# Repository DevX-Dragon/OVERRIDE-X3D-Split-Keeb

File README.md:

# OVERRIDE-X3D Split Keeb
A split keyboard from-scratch, high-performance wireless split keyboard designed for ergonomic uses.

## Layout

## Renders
#### Assembled Render

#### PCB Render

## Firmware
This keyboard runs on **CircuitPython** using the **Adafruit HID library**. Unlike compiled firmware, you can edit your keymap by simply modifying the **code.py** file directly on the keyboard's internal storage.

#### Libraries
To run this firmware, you need the following libraries in your /lib folder:

**adafruit_hid** (For Keyboard and Consumer Control support)

**adafruit_ble** (For wireless Bluetooth connectivity)

## BOM
(note that this is where I purchased from, and some are bought in higher quanities then needed for cheaper prices and some websites are local-only)
| Product Name | Quantity | Source Link | Price |
| :--- | :--- | :--- | :--- |
| 1N4148 | 42 | [Link](https://www.duino.lk/product/x-1n4148-diode-in4148-4148-switching-diode/) | $0.60 |
| SK6812 MINI-E | 8 | [Link](http://www.aliexpress.com/item/1005008308801366.html) | $1.56 |
| 820K Ohms THT Resistor | 2 | [Link](https://www.duino.lk/product/820k-ohm-1-4w-820k-5-carbon-film-resistor/) | $0.30 |
| 1M Ohms THT Ressitor | 4 | [Link](https://www.duino.lk/product/1m-ohm-1-4w-1m-5-carbon-film-resistor/) | $0.30 |
| OUTEMU Red Switches | 42 | [Link](https://share.temu.com/CwgZ9XWDBxB) | $13.74 |
| Milk Theme XDA Key Caps | 42 | [Link](https://www.aliexpress.com/item/1005009136116760.html) | $10.83 |
| 800mAh 3.7V 501845P Battery | 2 | [Link](https://www.duino.lk/product/800mah-3-7v-501845p-lipo-battery/) | $3.00 |
| Seed Studio Seeed XIAO-nRF52840-Sense | 2 | [Link](https://www.aliexpress.com/item/1005007426899386.html) | $43.12 |
| **Total** | | | **$73.45** |

> The reason for using the Seed Studio Seeed XIAO-nRF52840-Sense is becuase thats the only compact MCU which has enough pins for this. The esp32-s3 is another alternative but doesnt have pins to control the LEDs. So I had to go with this. There are no other MCU thats fits in the same size and have the same amount of pins.

## Support
I would love getting financially supported as most of my projects cost alot of money here in Sri Lanka. Even a 1$ is great!

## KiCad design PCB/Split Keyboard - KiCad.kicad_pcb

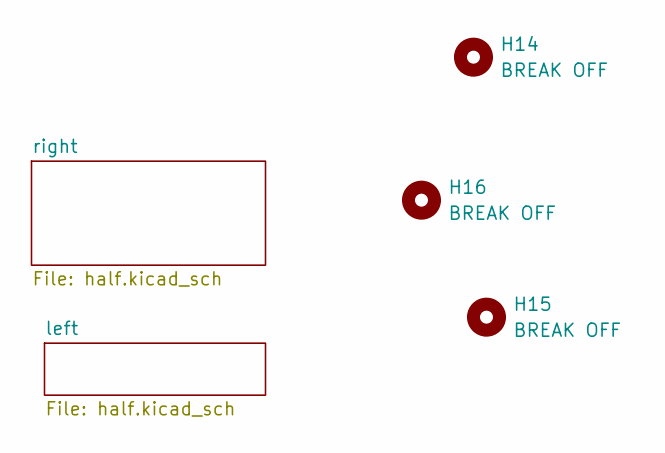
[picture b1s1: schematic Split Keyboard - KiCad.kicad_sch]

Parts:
H14, H15, H16: BREAK OFF; mouse-bite-5mm-slot

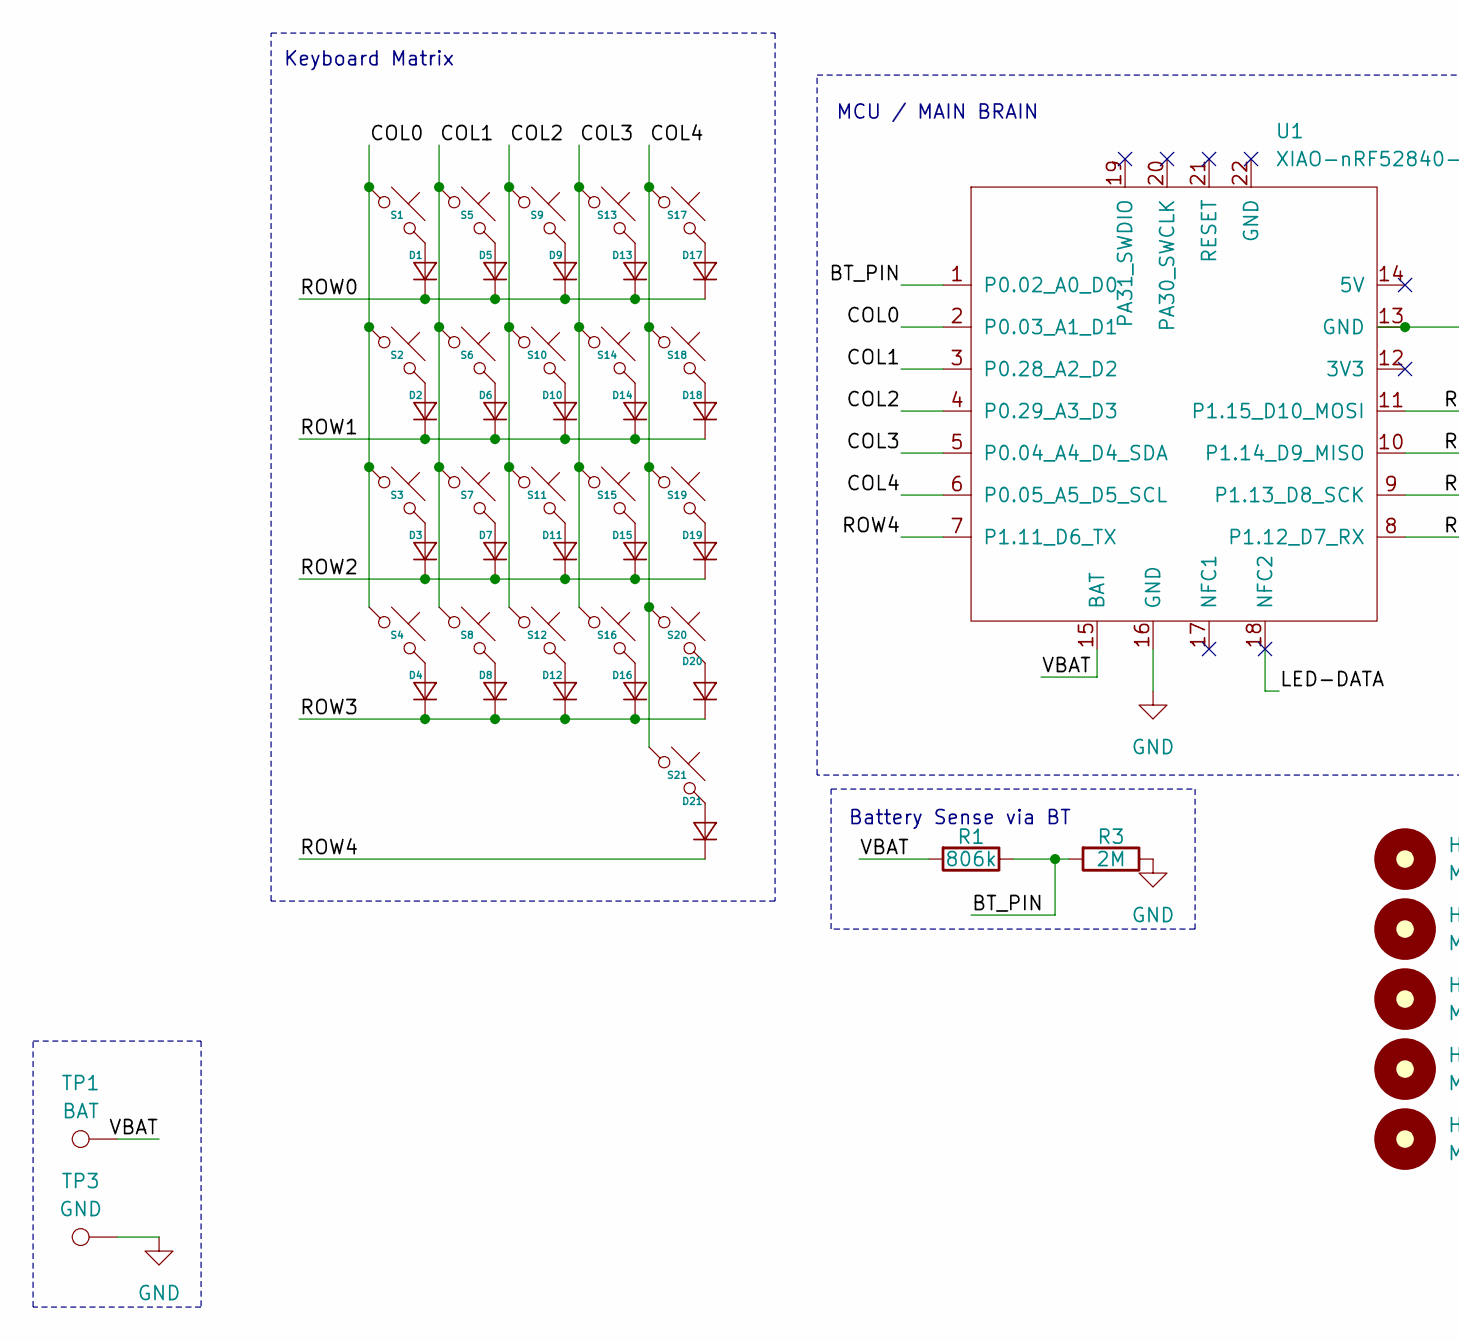
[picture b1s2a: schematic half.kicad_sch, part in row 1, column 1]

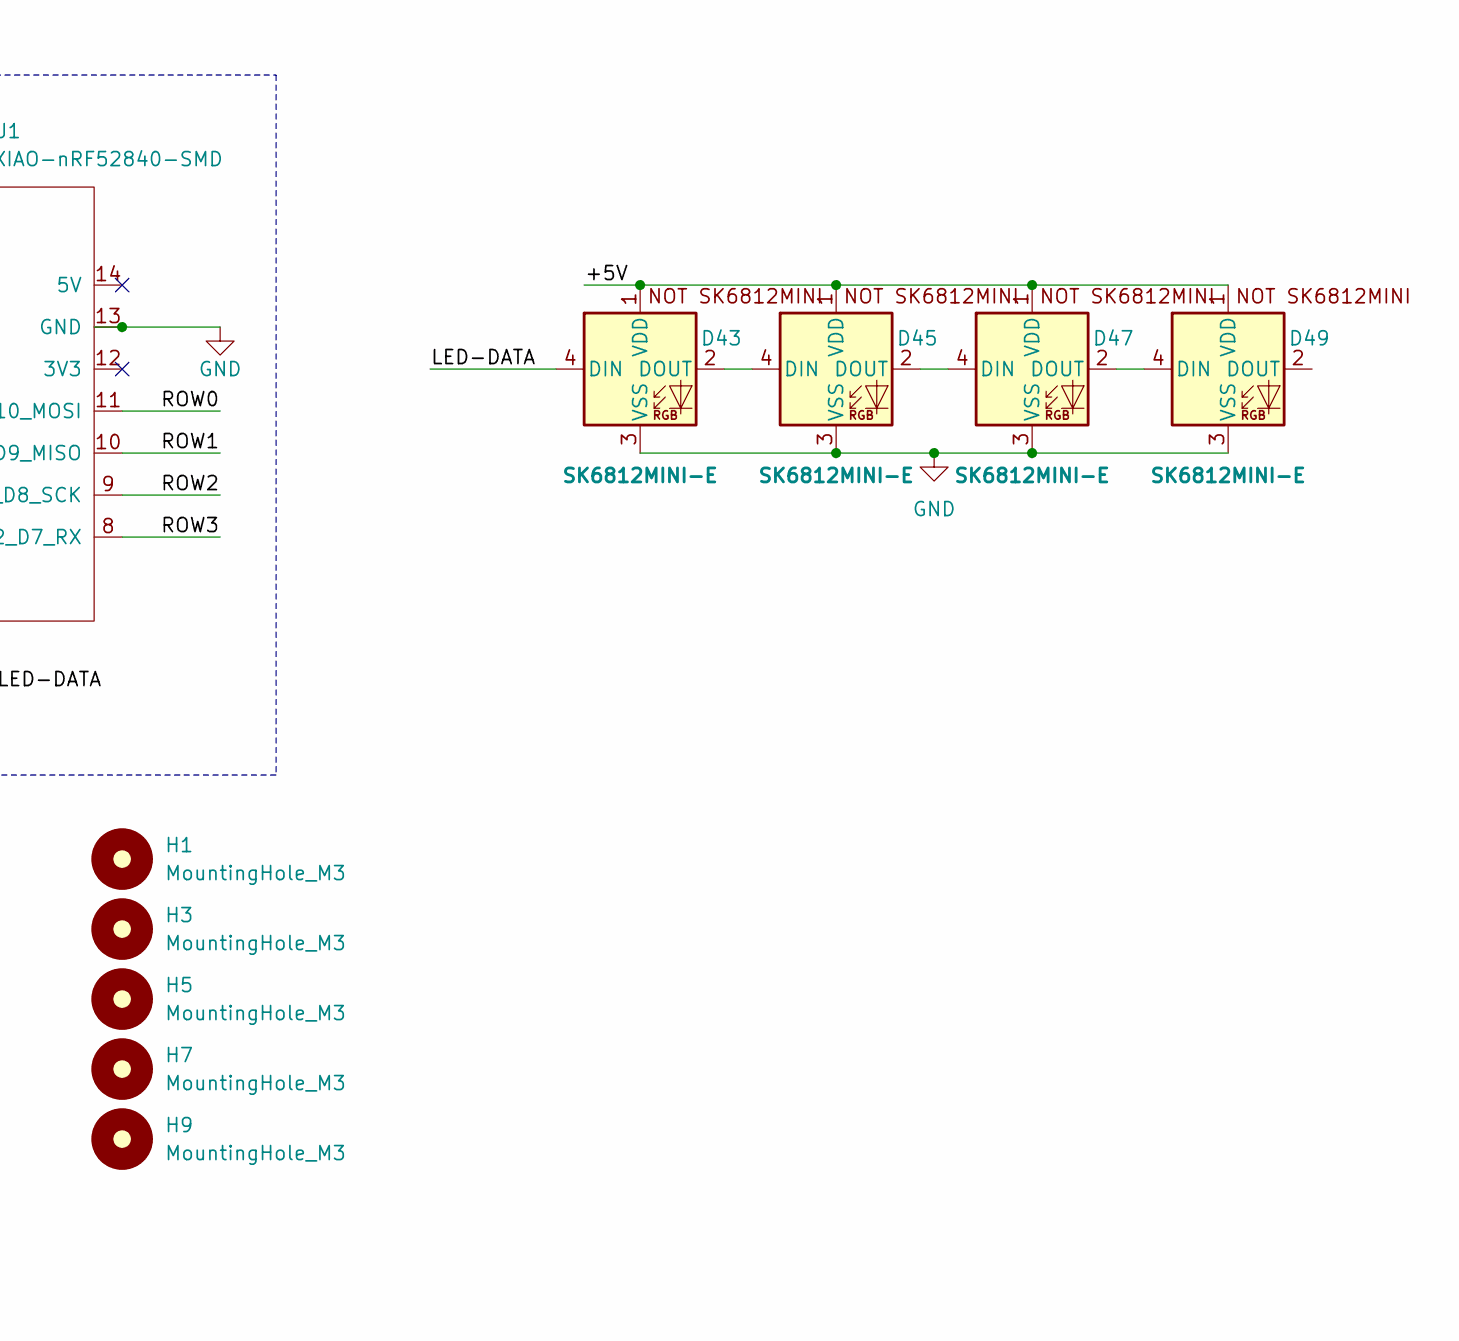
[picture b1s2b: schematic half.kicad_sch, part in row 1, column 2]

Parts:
D1, D2, D3, D4, D5, D6, D7, D8, D9, D10, D11, D12, D13, D14, D15, D16, D17, D18, D19, D20, D21: Diode_DO-35
D43, D45, D47, D49: SK6812MINI-E; SK6812MINI-E_fixed
H1, H3, H5, H7, H9: MountingHole_M3; MountingHole_3.2mm_M3
R1: 806k; R_Axial_DIN0204_L3.6mm_D1.6mm_P5.08mm_Horizontal
R3: 2M; R_Axial_DIN0204_L3.6mm_D1.6mm_P5.08mm_Horizontal
S1, S2, S3, S4, S5, S6, S7, S8, S9, S10, S11, S12, S13, S14, S15, S16, S17, S18, S19, S20, S21: MX_PCB_1.00u
TP1: BAT; TestPoint_Pad_D2.0mm
TP3: GND; TestPoint_Pad_D2.0mm
U1: XIAO-nRF52840-SMD; modified-XIAO-nRF52840-SMD

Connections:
/right/+5V: D43.1 (VDD), D45.1 (VDD), D47.1 (VDD), D49.1 (VDD)
/right/BT_PIN: R1.1, R3.2, U1.1 (P0.02_A0_D0)
/right/COL0: S1.1, S2.1, S3.1, S4.1, U1.2 (P0.03_A1_D1)
/right/COL1: S5.1, S6.1, S7.1, S8.1, U1.3 (P0.28_A2_D2)
/right/COL2: S9.1, S10.1, S11.1, S12.1, U1.4 (P0.29_A3_D3)
/right/COL3: S13.1, S14.1, S15.1, S16.1, U1.5 (P0.04_A4_D4_SDA)
/right/COL4: S17.1, S18.1, S19.1, S20.1, S21.1, U1.6 (P0.05_A5_D5_SCL)
/right/LED-DATA: D43.4 (DIN), U1.18 (NFC2)
/right/ROW0: D1.1 (K), D5.1 (K), D9.1 (K), D13.1 (K), D17.1 (K), U1.11 (P1.15_D10_MOSI)
/right/ROW1: D2.1 (K), D6.1 (K), D10.1 (K), D14.1 (K), D18.1 (K), U1.10 (P1.14_D9_MISO)
/right/ROW2: D3.1 (K), D7.1 (K), D11.1 (K), D15.1 (K), D19.1 (K), U1.9 (P1.13_D8_SCK)
/right/ROW3: D4.1 (K), D8.1 (K), D12.1 (K), D16.1 (K), D20.1 (K), U1.8 (P1.12_D7_RX)
/right/ROW4: D21.1 (K), U1.7 (P1.11_D6_TX)
/right/VBAT: R1.2, TP1.1, U1.15 (BAT)
GND: D43.3 (VSS), D45.3 (VSS), D47.3 (VSS), D49.3 (VSS), R3.1, TP3.1, U1.13 (GND), U1.16 (GND); also elsewhere on the board
unnamed: D1.2 (A), S1.2
unnamed: D2.2 (A), S2.2
unnamed: D3.2 (A), S3.2
unnamed: D4.2 (A), S4.2
unnamed: D5.2 (A), S5.2
unnamed: D6.2 (A), S6.2
unnamed: D7.2 (A), S7.2
unnamed: D8.2 (A), S8.2
unnamed: D9.2 (A), S9.2
unnamed: D10.2 (A), S10.2
unnamed: D11.2 (A), S11.2
unnamed: D12.2 (A), S12.2
unnamed: D13.2 (A), S13.2
unnamed: D14.2 (A), S14.2
unnamed: D15.2 (A), S15.2
unnamed: D16.2 (A), S16.2
unnamed: D17.2 (A), S17.2
unnamed: D18.2 (A), S18.2
unnamed: D19.2 (A), S19.2
unnamed: D20.2 (A), S20.2
unnamed: D21.2 (A), S21.2
unnamed: D43.2 (DOUT), D45.4 (DIN)
unnamed: D45.2 (DOUT), D47.4 (DIN)
unnamed: D47.2 (DOUT), D49.4 (DIN)

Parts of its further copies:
D22, D23, D24, D25, D26, D27, D28, D29, D30, D31, D32, D33, D34, D35, D36, D37, D38, D39, D40, D41, D42: Diode_DO-35
D44, D46, D48, D50: SK6812MINI-E; SK6812MINI-E_fixed
H2, H4, H6, H8, H10: MountingHole_M3; MountingHole_3.2mm_M3
R2: 806k; R_Axial_DIN0204_L3.6mm_D1.6mm_P5.08mm_Horizontal
R4: 2M; R_Axial_DIN0204_L3.6mm_D1.6mm_P5.08mm_Horizontal
S22, S23, S24, S25, S26, S27, S28, S29, S30, S31, S32, S33, S34, S35, S36, S37, S38, S39, S40, S41, S42: MX_PCB_1.00u
TP2: BAT; TestPoint_Pad_D2.0mm
TP4: GND; TestPoint_Pad_D2.0mm
U2: XIAO-nRF52840-SMD; modified-XIAO-nRF52840-SMD

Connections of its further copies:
/left/+5V: D44.1 (VDD), D46.1 (VDD), D48.1 (VDD), D50.1 (VDD)
/left/BT_PIN: R2.1, R4.2, U2.1 (P0.02_A0_D0)
/left/COL0: S22.1, S23.1, S24.1, S25.1, U2.2 (P0.03_A1_D1)
/left/COL1: S26.1, S27.1, S28.1, S29.1, U2.3 (P0.28_A2_D2)
/left/COL2: S30.1, S31.1, S32.1, S33.1, U2.4 (P0.29_A3_D3)
/left/COL3: S34.1, S35.1, S36.1, S37.1, U2.5 (P0.04_A4_D4_SDA)
/left/COL4: S38.1, S39.1, S40.1, S41.1, S42.1, U2.6 (P0.05_A5_D5_SCL)
/left/LED-DATA: D44.4 (DIN), U2.18 (NFC2)
/left/ROW0: D22.1 (K), D26.1 (K), D30.1 (K), D34.1 (K), D38.1 (K), U2.11 (P1.15_D10_MOSI)
/left/ROW1: D23.1 (K), D27.1 (K), D31.1 (K), D35.1 (K), D39.1 (K), U2.10 (P1.14_D9_MISO)
/left/ROW2: D24.1 (K), D28.1 (K), D32.1 (K), D36.1 (K), D40.1 (K), U2.9 (P1.13_D8_SCK)
/left/ROW3: D25.1 (K), D29.1 (K), D33.1 (K), D37.1 (K), D41.1 (K), U2.8 (P1.12_D7_RX)
/left/ROW4: D42.1 (K), U2.7 (P1.11_D6_TX)
/left/VBAT: R2.2, TP2.1, U2.15 (BAT)
GND: D44.3 (VSS), D46.3 (VSS), D48.3 (VSS), D50.3 (VSS), R4.1, TP4.1, U2.13 (GND), U2.16 (GND); also elsewhere on the board
unnamed: D22.2 (A), S22.2
unnamed: D23.2 (A), S23.2
unnamed: D24.2 (A), S24.2
unnamed: D25.2 (A), S25.2
unnamed: D26.2 (A), S26.2
unnamed: D27.2 (A), S27.2
unnamed: D28.2 (A), S28.2
unnamed: D29.2 (A), S29.2
unnamed: D30.2 (A), S30.2
unnamed: D31.2 (A), S31.2
unnamed: D32.2 (A), S32.2
unnamed: D33.2 (A), S33.2
unnamed: D34.2 (A), S34.2
unnamed: D35.2 (A), S35.2
unnamed: D36.2 (A), S36.2
unnamed: D37.2 (A), S37.2
unnamed: D38.2 (A), S38.2
unnamed: D39.2 (A), S39.2
unnamed: D40.2 (A), S40.2
unnamed: D41.2 (A), S41.2
unnamed: D42.2 (A), S42.2
unnamed: D44.2 (DOUT), D46.4 (DIN)
unnamed: D46.2 (DOUT), D48.4 (DIN)
unnamed: D48.2 (DOUT), D50.4 (DIN)

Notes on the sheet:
Keyboard Matrix
MCU / MAIN BRAIN
Battery Sense via BT

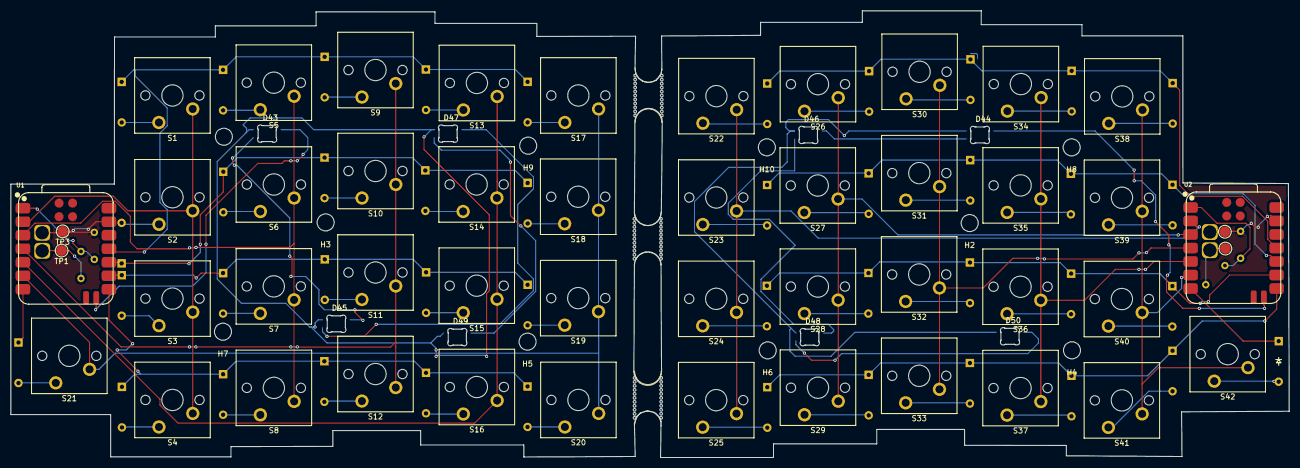
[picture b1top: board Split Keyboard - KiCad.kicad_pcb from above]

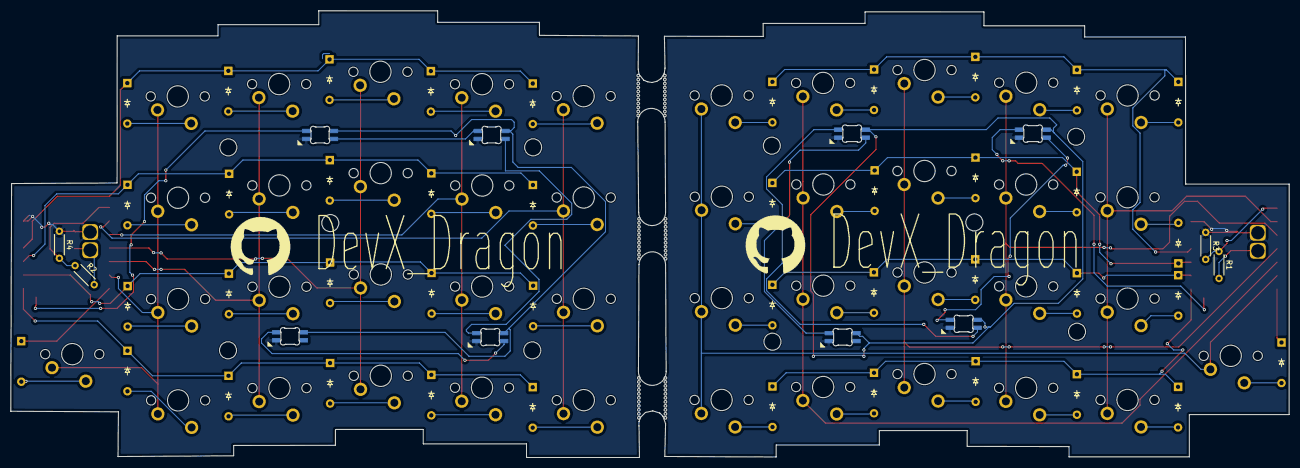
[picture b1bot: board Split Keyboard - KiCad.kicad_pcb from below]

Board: 2 copper layers, 240.3 x 83.9 mm, 115 parts (45 on the bottom side), 77 nets.

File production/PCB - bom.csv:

Designator,Footprint,Quantity,Value,LCSC Part #
"D1, D10, D11, D12, D13, D14, D15, D16, D17, D18, D19, D2, D20, D21, D22, D23, D24, D25, D26, D27, D28, D29, D3, D30, D31, D32, D33, D34, D35, D36, D37, D38, D39, D4, D40, D41, D42, D5, D6, D7, D8, D9",Diode_DO-35,42,~,
"D43, D44, D45, D46, D47, D48, D49, D50",SK6812MINI-E_fixed,8,SK6812MINI-E,
"H1, H10, H2, H3, H4, H5, H6, H7, H8, H9",MountingHole_3.2mm_M3,10,MountingHole_M3,
"R1, R2",R_Axial_DIN0204_L3.6mm_D1.6mm_P5.08mm_Horizontal,2,806k,
"R3, R4",R_Axial_DIN0204_L3.6mm_D1.6mm_P5.08mm_Horizontal,2,2M,
"S1, S10, S11, S12, S13, S14, S15, S16, S17, S18, S19, S2, S20, S21, S22, S23, S24, S25, S26, S27, S28, S29, S3, S30, S31, S32, S33, S34, S35, S36, S37, S38, S39, S4, S40, S41, S42, S5, S6, S7, S8, S9",MX_PCB_1.00u,42,~,
"TP1, TP2",TestPoint_Pad_D2.0mm,2,BAT,
"TP3, TP4",TestPoint_Pad_D2.0mm,2,GND,
"U1, U2",modified-XIAO-nRF52840-SMD,2,XIAO-nRF52840-SMD,

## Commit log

2026-02-01 Adding All
2026-02-12 HAD TO ZIP THE MCAUSE BIGGY
    HAD TO ZIP THEM CAUSE BIG AND I DONT USE GIT FOR MY WORKS AS MY LAPTOP WONT RUN IT PROPERLY
2026-02-13 Adding assembled preview in step files
